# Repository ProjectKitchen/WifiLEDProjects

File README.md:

# WifiLEDProjects
ESP8266-based Ledpixel projects based on Workshop by Rui (Ray) Wang - thanks to Ray !!

visit: http://rayshobby.net/?p=10963   

watch: https://www.youtube.com/watch?v=ZKuIWDocIiM

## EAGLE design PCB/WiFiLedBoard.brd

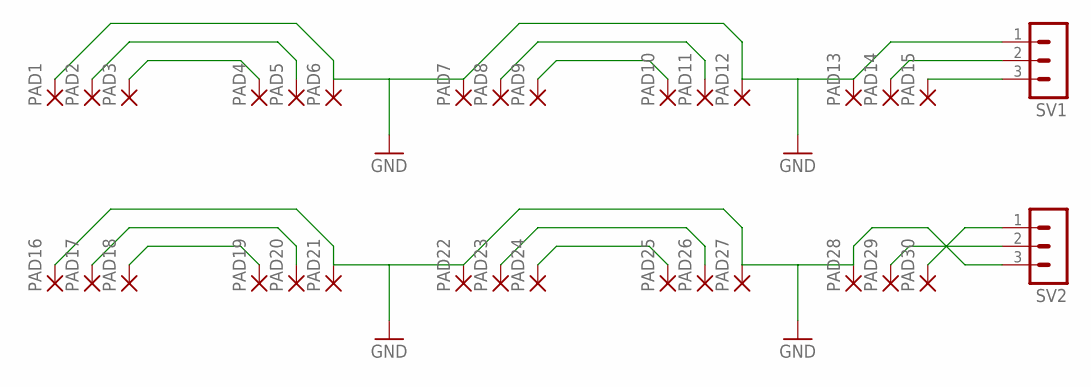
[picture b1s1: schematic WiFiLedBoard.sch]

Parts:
PAD1, PAD2, PAD3, PAD4, PAD5, PAD6, PAD7, PAD8, PAD9, PAD10, PAD11, PAD12, PAD13, PAD14, PAD15, PAD16, PAD17, PAD18, PAD19, PAD20, PAD21, PAD22, PAD23, PAD24, PAD25, PAD26, PAD27, PAD28, PAD29, PAD30: SMD2; SMD1,27-2,54
SV1, SV2: MA03-1

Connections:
GND: PAD1.1, PAD6.1, PAD7.1, PAD12.1, PAD13.1, PAD16.1, PAD21.1, PAD22.1, PAD27.1, PAD28.1, SV1.1, SV2.3
unnamed: PAD3.1, PAD4.1
unnamed: PAD2.1, PAD5.1
unnamed: PAD9.1, PAD10.1
unnamed: PAD8.1, PAD11.1
unnamed: PAD14.1, SV1.2
unnamed: PAD29.1, SV2.2
unnamed: PAD30.1, SV2.1
unnamed: PAD18.1, PAD19.1
unnamed: PAD17.1, PAD20.1
unnamed: PAD24.1, PAD25.1
unnamed: PAD23.1, PAD26.1
unnamed: PAD15.1, SV1.3

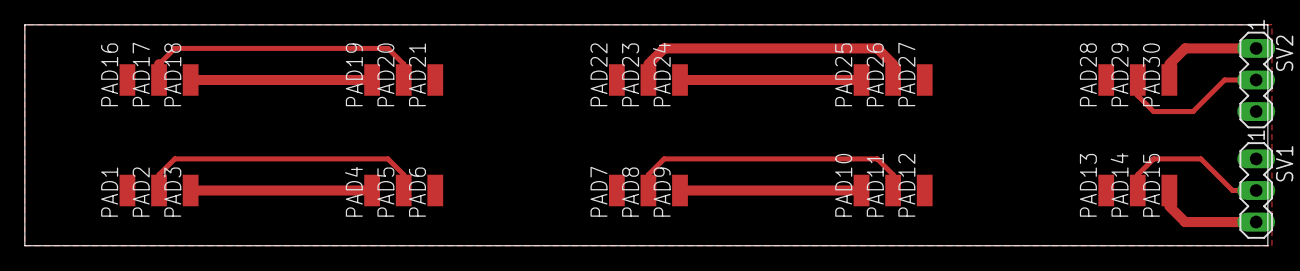
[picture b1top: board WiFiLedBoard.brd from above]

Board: 2 copper layers, 100.0 x 17.8 mm, 32 parts (0 on the bottom side), 13 nets.

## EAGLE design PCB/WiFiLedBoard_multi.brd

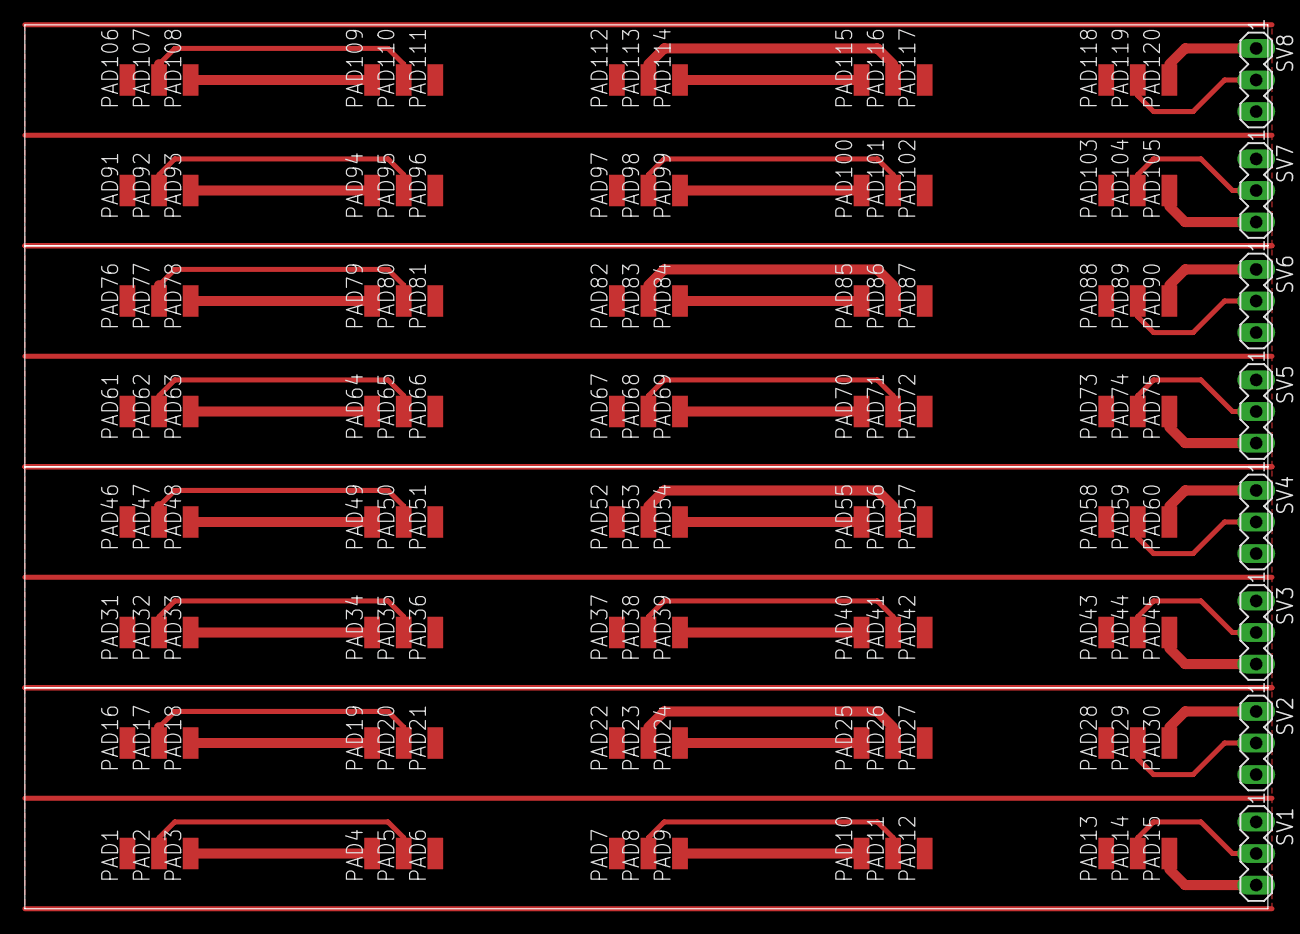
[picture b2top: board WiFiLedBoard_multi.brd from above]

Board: 2 copper layers, 100.0 x 71.1 mm, 128 parts (0 on the bottom side), 52 nets.

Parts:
PAD1, PAD2, PAD3, PAD4, PAD5, PAD6, PAD7, PAD8, PAD9, PAD10, PAD11, PAD12, PAD13, PAD14, PAD15, PAD16, PAD17, PAD18, PAD19, PAD20, PAD21, PAD22, PAD23, PAD24, PAD25, PAD26, PAD27, PAD28, PAD29, PAD30, PAD31, PAD32, PAD33, PAD34, PAD35, PAD36, PAD37, PAD38, PAD39, PAD40, PAD41, PAD42, PAD43, PAD44, PAD45, PAD46, PAD47, PAD48, PAD49, PAD50, PAD51, PAD52, PAD53, PAD54, PAD55, PAD56, PAD57, PAD58, PAD59, PAD60, PAD61, PAD62, PAD63, PAD64, PAD65, PAD66, PAD67, PAD68, PAD69, PAD70, PAD71, PAD72, PAD73, PAD74, PAD75, PAD76, PAD77, PAD78, PAD79, PAD80, PAD81, PAD82, PAD83, PAD84, PAD85, PAD86, PAD87, PAD88, PAD89, PAD90, PAD91, PAD92, PAD93, PAD94, PAD95, PAD96, PAD97, PAD98, PAD99, PAD100, PAD101, PAD102, PAD103, PAD104, PAD105, PAD106, PAD107, PAD108, PAD109, PAD110, PAD111, PAD112, PAD113, PAD114, PAD115, PAD116, PAD117, PAD118, PAD119, PAD120: SMD1,27-2,54
SV1, SV2, SV3, SV4, SV5, SV6, SV7, SV8: MA03-1

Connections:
GND: PAD1.1, PAD6.1, PAD7.1, PAD12.1, PAD13.1, PAD16.1, PAD21.1, PAD22.1, PAD27.1, PAD28.1, SV1.1, SV2.3
GND1: PAD31.1, PAD36.1, PAD37.1, PAD42.1, PAD43.1, PAD46.1, PAD51.1, PAD52.1, PAD57.1, PAD58.1, SV3.1, SV4.3
GND2: PAD61.1, PAD66.1, PAD67.1, PAD72.1, PAD73.1, PAD76.1, PAD81.1, PAD82.1, PAD87.1, PAD88.1, SV5.1, SV6.3
GND3: PAD91.1, PAD96.1, PAD97.1, PAD102.1, PAD103.1, PAD106.1, PAD111.1, PAD112.1, PAD117.1, PAD118.1, SV7.1, SV8.3
unnamed: PAD3.1, PAD4.1
unnamed: PAD2.1, PAD5.1
unnamed: PAD9.1, PAD10.1
unnamed: PAD8.1, PAD11.1
unnamed: PAD14.1, SV1.2
unnamed: PAD29.1, SV2.2
unnamed: PAD30.1, SV2.1
unnamed: PAD18.1, PAD19.1
unnamed: PAD17.1, PAD20.1
unnamed: PAD33.1, PAD34.1
unnamed: PAD24.1, PAD25.1
unnamed: PAD23.1, PAD26.1
unnamed: PAD32.1, PAD35.1
unnamed: PAD39.1, PAD40.1
unnamed: PAD15.1, SV1.3
unnamed: PAD38.1, PAD41.1
unnamed: PAD48.1, PAD49.1
unnamed: PAD47.1, PAD50.1
unnamed: PAD54.1, PAD55.1
unnamed: PAD53.1, PAD56.1
unnamed: PAD44.1, SV3.2
unnamed: PAD59.1, SV4.2
unnamed: PAD60.1, SV4.1
unnamed: PAD45.1, SV3.3
unnamed: PAD63.1, PAD64.1
unnamed: PAD62.1, PAD65.1
unnamed: PAD69.1, PAD70.1
unnamed: PAD68.1, PAD71.1
unnamed: PAD78.1, PAD79.1
unnamed: PAD77.1, PAD80.1
unnamed: PAD84.1, PAD85.1
unnamed: PAD83.1, PAD86.1
unnamed: PAD74.1, SV5.2
unnamed: PAD89.1, SV6.2
unnamed: PAD90.1, SV6.1
unnamed: PAD75.1, SV5.3
unnamed: PAD93.1, PAD94.1
unnamed: PAD92.1, PAD95.1
unnamed: PAD99.1, PAD100.1
unnamed: PAD98.1, PAD101.1
unnamed: PAD108.1, PAD109.1
unnamed: PAD107.1, PAD110.1
unnamed: PAD114.1, PAD115.1
unnamed: PAD113.1, PAD116.1
unnamed: PAD104.1, SV7.2
unnamed: PAD119.1, SV8.2
unnamed: PAD120.1, SV8.1
unnamed: PAD105.1, SV7.3

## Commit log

2017-04-01 added files
2017-04-01 updated links
2026-04-02 support default message, default icon and auto reset after timeout
